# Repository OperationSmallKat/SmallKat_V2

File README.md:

# Small Kat Quadruped

The SmallKat project is a low cost, opensource, 3D printed quadrupedal platform designed and made by 2 WPI students (Keion Bisland and Xavier Little) along with framework code prepared by Kevin Harrington. The intention of the platform was to make a dynamics quadruped for the education/research and high-end toy markets. Using hobby servos and common electronics allows the overall price point to remain very low in comparison to its competitors. 

SmallKat comes in 3 sizes, micro, small and xl. Micro is the smallest and at one pound, is the same size and weight as a kitten. Small is the current product offering and is availible in 2 different electronics solutions. XL is a research grade platform and is the product of an MQP at WPI. 

The simple electronics platform is a single ESP32, 16 servos, 3 switch mode BEC's and a BNO055 IMU.  This platform is easiest to source assemble using of OTS parts plus printed pieces. This platform streams sensor data up, and servo positions down, using the WiFi built into the ESP32. This configuration is easy to develop for because the code kinematics/walking gait code runs on a nearby PC. Kinematics and walking gait/body controllers can be swapped out on-the-fly without restarting SmallKats controller making development fast. Once algorithms are finalized and published to Git, they can be loaded by the second configuration and run in a tight real-time loop with the hardware. A downside to this configuration is that it is only as stable as your WiFi signal in the room. 

The advanced configuration uses the same control coda as the Wifi version, except it loads a headless kernel and runs it  on a RasPi onboard of the robot. This configuration uses an STM32 to connect to the BNO055 and servos, and bridge them directly to the onboard RasPi over HID.  The first variant used a Teensy, but we wish for the full stack to be fully open source and so are switching to a custom STM32 board.  This solution will be more expensive, and development loops will include pusing to a git server and re-starting the robots control stack to load new code. These trade offs suggest that both electronics solutions ought to exist as options, and researchers might want both in a given lab. Toy markets would only be interested in this type of fully stand-alone electronics, since it requires no setup to start the robot running.

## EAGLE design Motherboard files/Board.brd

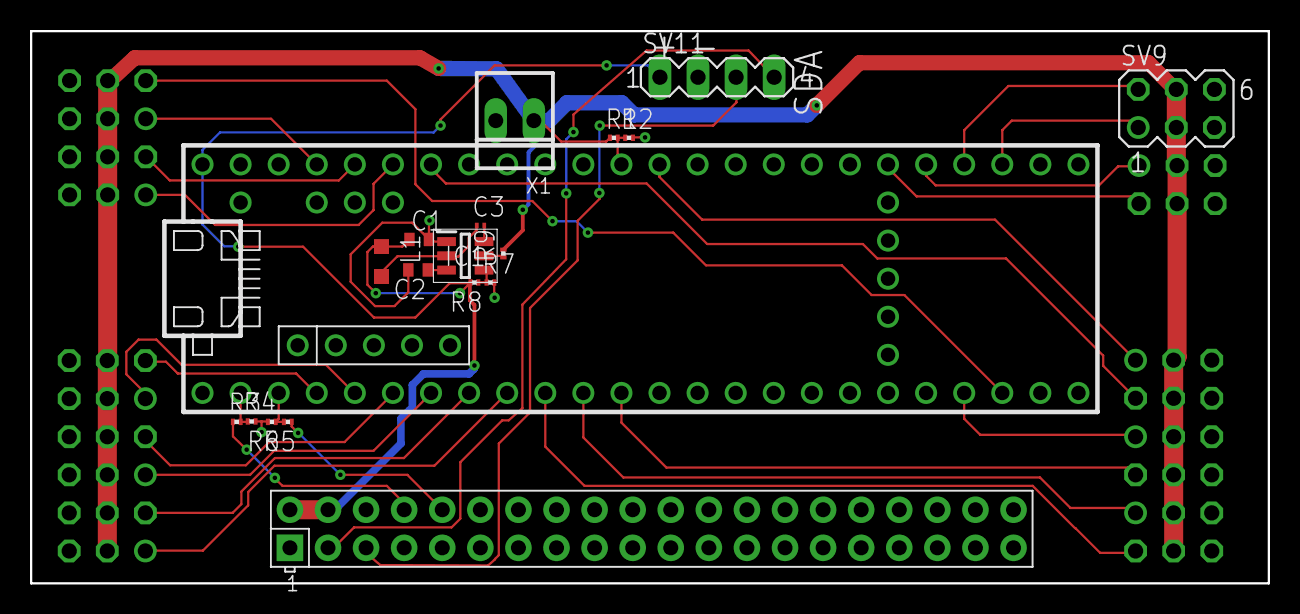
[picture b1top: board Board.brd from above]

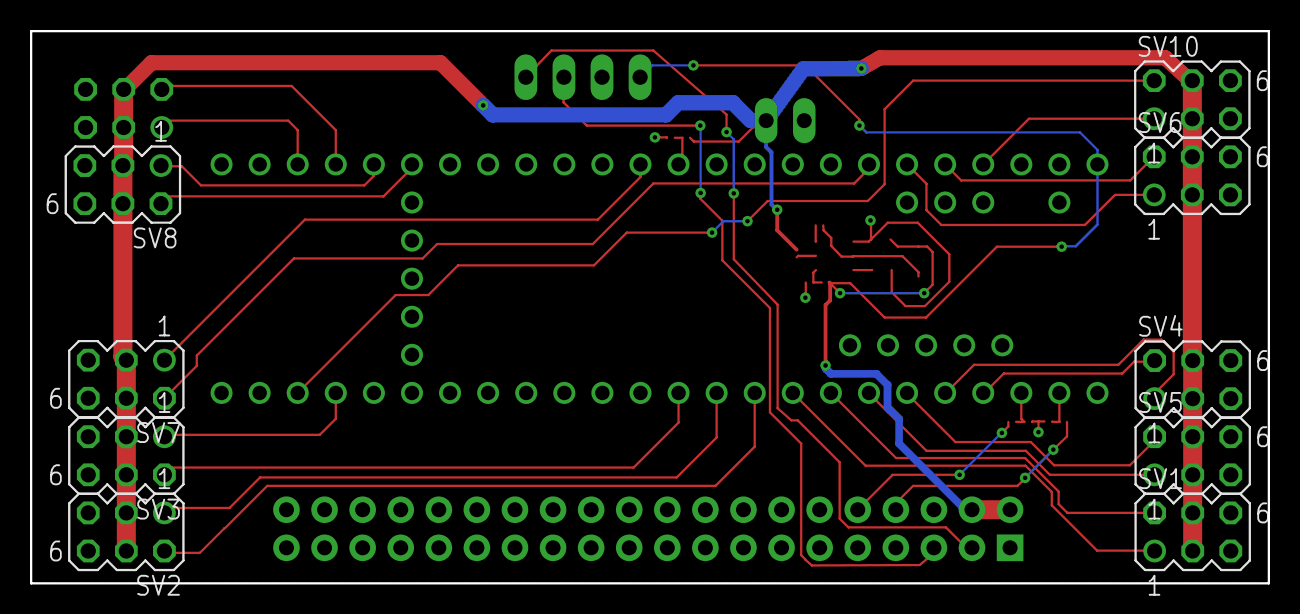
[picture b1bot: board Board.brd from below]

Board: 2 copper layers, 82.5 x 36.8 mm, 28 parts (9 on the bottom side), 35 nets.

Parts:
C1, C2: C0402
C3: C0201
IC1: TPS562209DDCR; SOT95P280X110-6N
L1: L2012C
R1, R2, R3, R4, R5, R6, R7, R8, R9: R0201
SV1, SV2, SV3, SV4, SV5, SV6, SV7, SV8, SV9, SV10: MA03-2
SV11: MA04-1
U$1: RPI-ZERO; RASPBERRYPI_BASTELSTUBE_V13_RASPI_BOARD_B+_FULL
U$2: TEENSY_3.5/3.6
X1: 22-23-2021

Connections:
+5V: C1.1, L1.1, R8.2, SV11.1, U$1.2, U$1.4, U$2.VIN
BATTCHECK: R1.2, R2.1, U$2.15/A1
GND: C1.2, C2.2, IC1.1, R2.2, R4.2, R6.2, R7.2, SV1.5, SV1.6, SV2.5, SV2.6, SV3.5, SV3.6, SV4.5, SV4.6, SV5.5, SV5.6, SV6.5, SV6.6, SV7.5, SV7.6, SV8.5, SV8.6, SV9.5, SV9.6, SV10.5, SV10.6, SV11.2, U$1.6, U$1.9, U$1.14, U$1.20, U$1.25, U$1.30, U$1.34, U$1.39, U$2.AGND, U$2.GND, U$2.GND2, X1.2
unnamed: C3.1, IC1.2, L1.2
unnamed: C2.1, IC1.3
unnamed: C3.2, IC1.6
unnamed: IC1.5, R9.1
unnamed: IC1.4, R7.1, R8.1
RPIRX: R5.1, U$1.10
RPITX: R3.1, U$1.8
RX: R3.2, R4.1, U$2.0/RX
S1: SV4.2, U$2.2
S2: SV4.1, U$2.3/CANTX
S3: SV5.2, U$2.4/CANRX
S4: SV5.1, U$2.5
S5: SV1.2, U$2.6
S6: SV1.1, U$2.7
S7: SV2.2, U$2.8
S8: SV2.1, U$2.9/CS
S9: SV3.2, U$2.10/CS
S10: SV3.1, U$2.29
S11: SV10.2, U$2.30
S12: SV10.1, U$2.23/A9
S13: SV6.2, U$2.22/A8
S14: SV6.1, U$2.21/A7
S15: SV7.2, U$2.20/A6
S16: SV7.1, U$2.14/A0
S17: SV8.2, U$2.38/A19
S18: SV8.1, U$2.37/A18
S19: SV9.2, U$2.36/A17
S20: SV9.1, U$2.35/A16
SCL: SV11.3, U$1.5
SDA: SV11.4, U$1.3
TX: R5.2, R6.1, U$2.1/TX
VCC: R1.1, R9.2, SV1.3, SV1.4, SV2.3, SV2.4, SV3.3, SV3.4, SV4.3, SV4.4, SV5.3, SV5.4, SV6.3, SV6.4, SV7.3, SV7.4, SV8.3, SV8.4, SV9.3, SV9.4, SV10.3, SV10.4, X1.1

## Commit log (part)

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2018-05-18 MediumKat STL files
2018-05-18 Added MKBody
2018-05-18 added the lowe limbs
2018-05-18 all STL files updated
2018-05-18 first limb update
2018-05-18 lims corrected
2018-05-18 first leg placement working
2018-05-18 renamed limbs
2018-05-18 working on DH parameters
2018-05-18 Fixed Legs
2018-05-18 Leg DH parameters and config
2018-05-18 Edited legs
2018-05-18 added tail and head files
2018-05-18 tried to add cat and head
2018-05-19 head and tail index update
2018-05-19 head and tail loading
2018-05-19 updating link indexes
2018-05-19 non-overlapping links
2018-05-19 orentation of neack matches links
2018-05-19 allignment of neck stl
2018-05-19 neck location
2018-05-19 head and tail root locations
2018-05-19 base of limbs and D-H for neck and tail
2018-05-19 head located
2018-05-19 all cat parts loading nicely
2018-05-19 all cat parts loading
2018-05-19 shoulder reorentation
2018-05-19 walking engine loaded
2018-05-19 working defaults
2018-05-19 right rear boundaries
2018-05-19 front left bounded
2018-05-19 dynamic walk cycle
2018-05-20 step reset working
2018-05-21 adding the simple API
2018-05-21 syntax
2018-05-21 IMU and servo device
2018-05-21 adding the import for IMU
2018-05-21 update vidpid pair
2018-05-21 better printouts
2018-05-21 updating the IMU data
2018-05-21 tighter gait
2018-05-21 updated the link angles
2018-05-21 wider hip kinematics
2018-05-21 calculating the gat section percentages based on time
2018-05-22 step step down working in slow mo
2018-05-22 rear left adjusted
2018-05-22 walking in tuning
2018-05-22 mostly working trot gait
2018-05-22 mystery step reset issue
2018-05-22 no runaway feet
2018-05-22 foot cycling for up section
2018-05-22 dynamic walking gait
2018-05-22 smaller transit to home
2018-05-22 drift fix
2018-05-22 no prints
2018-05-22 trapazoidal foot motion profile
2018-05-22 modular cycle grouping
2018-05-22 working dynamic wave gait
2018-05-22 adding IMU print to dynamics
2018-05-22 adding listeners
2018-05-22 removing IMU in loop
2018-05-22 IMU integrated into walking gait
2018-05-22 dynamic gait
2018-05-22 normal speed
2018-05-22 adjustable pan and tilt values
2018-05-22 normal shoulder gait
2018-05-22 parametric static offsets
2018-05-22 latest dynamics
2018-05-22 Walking (#4)
    * trapazoidal foot motion profile
    * modular cycle grouping
    * working dynamic wave gait
    * adding IMU print to dynamics
    * adding listeners
    * removing IMU in loop
2018-05-23 removing dead links
2018-05-23 removed stub links
2018-05-23 catch NPE
2018-05-23 ensuring push
2018-05-24 Config
2018-05-24 updated upper and lower bounds
2018-05-24 updated centers
2018-05-24 updated a theta
2018-05-24 changing dh parameters
2018-05-24 50.80
2018-05-25 adding coriolius updater
2018-05-25 swagger
2018-05-25 adding the timeouts back in
2018-05-25 smooth bobbing to shif balence
2018-05-25 at-speed walking with head and tail bob
2018-05-25 heat crests at the weaight shift point
2018-05-25 standard smoothed bobbing unless UMU updates
2018-05-25 dynamic step gait timing
2018-05-25 adding dynamic speed updates
2018-05-25 dynamic loop speed based on ground speed
2018-05-25 cleaned up the step reset cycle trajectory loop
2018-05-25 full dynamics with all legs
2018-05-25 corrected maximum step size
2018-05-25 no motion when stopped
2018-05-25 full trajectory step cycle working
2018-05-25 catch teh multi-set exception
2018-05-25 proper step loop resetting
2018-05-25 time gap the recalulation loop
2018-05-25 using the step cycle count to determ pan value
2018-05-25 timeout of commands
2018-05-25 wait for the previous command to finish
2018-05-25 bound velocity but not overall translation
2018-05-25 cached the pose, lets use this as the target later
2018-05-25 set the global transform
2018-05-25 cached positions for avoiding collisions
2018-05-25 full stack full cycle walking gait, no hiicups
2018-05-25 working cycle
2018-05-26 adding possiblity checks to sets
2018-05-26 Force homing even is pathing errors occour
2018-05-26 attempt to use the set joint values first
2018-05-26 updaed dynamisc walking
2018-05-26 adding the tripod style gait
2018-05-26 modularized the building of the leg groups
2018-05-26 comments
2018-05-26 waiting on the timeout, not the timouut vatiable to accept a new command
2018-05-26 bount gait percentage to 1
2018-05-26 bounding the step lenght appropratly
2018-05-26 stop impossible pose update from executing
2018-05-26 fail out pose updates that are not possible
2018-05-26 parameterize the minimum step over time as the minimum gait time
2018-05-26 Dynamics (#5)
    * trapazoidal foot motion profile
    * modular cycle grouping
    * working dynamic wave gait
    * adding IMU print to dynamics
    * adding listeners
    * removing IMU in loop
2018-05-26 stop the head bob when stepping home
2018-05-27 boundary orented step calculations
2018-05-27 more complete checking of the possiblibility of a new update for a leg
2018-05-27 clearly bounding the possible foot locations and checking all extrema
2018-05-27 full cycle dynamics
2018-05-27 faster compute cycle
2018-05-27 timer reset by the main thread calls, not the walking thread calls
2018-05-27 startup state for first walk cycle starting in the current state
2018-05-27 sitting after steps timeout
2018-05-27 sitting at the end of a loop
2018-05-27 approoprate walking and sitting at the end of a loop
2018-05-27 updating the head and neck in the sit down loop
2018-05-27 smoother sitting
2018-05-27 sitting and standing interpolated based on loop timeing
2018-05-27 sleep in the correct space
2018-05-27 longer sit timeout
2018-05-27 Simulate the cat with custome physics engine
2018-05-27 adding basic physics
2018-05-28 catch exceptions in new pose
2018-05-28 calibrating...
2018-05-28 if not a Kat, do not sit
2018-05-28 Creating a robot loading script
2018-05-28 updating urls
2018-05-28 load cat from script side-loader
2018-05-28 fixed the limb link startup problem
2018-05-30 limits to keep gait happy
2018-05-30 filex the links bak, der
2018-05-30 adding tighter coriolis loop
2018-05-30 updated limits for kineamtics
2018-05-30 updated limits for kinematics
2018-05-31 Configuring Cat
2018-05-31 Configured
2018-06-03 Dynamics (#6)
    * limits to keep gait happy
    * filex the links bak, der
    * adding tighter coriolis loop
    * kinematics bounding
    * updated limits for kineamtics
    * updated limits for kinematics
2018-06-03 Adding arguments to the robot loading script
2018-06-03 adding parameters to the launch script call of the robot loader
2018-06-06 removed enum
2018-06-06 changing bottom link limits
2018-06-06 front feet a bit forward
2018-06-06 all gait cycles even
2018-06-06 remove dead code
2018-06-06 tighten the hip limits
2018-06-06 good speed over range
2018-06-06 adding tilt control
2018-06-06 moving leg back
2018-06-06 corrected pose
2018-06-06 posing is working
2018-06-06 better full speed turining
2018-06-06 fixed misallignment
2018-06-07 final calibration against hardware
2018-06-08 calibrated head and tail
2018-06-08 negative scale
2018-06-08 negative scales
2018-06-08 centered tail
2018-06-08 changed calibration
2018-06-08 Recalibrated
2018-06-12 Moved Firmware
2018-06-13 updaing URLs
2018-06-13 updaing URL's
2018-06-13 Removing files moved to new repos
2018-06-13 updating URL
2018-07-10 updated teh defaults
2018-07-10 changed home v alues
2018-07-17 calibrate
2018-07-17 reversing the hips
2018-07-18 use the UDP stack to get a udp version of the controller if its availible
2018-07-25 bugfix
2018-07-25 catch
2018-09-13 better prints
2018-09-13 using new controller API
2018-11-30 Updated order
2018-11-30 Updated head pinout
2018-11-30 updated stepover
2018-11-30 head range
2018-11-30 tal calibrate
2018-11-30 tail bounds
2018-11-30 rear conf
2018-11-30 calibrate legs
2018-11-30 faster timeout
2018-12-08 tweak limits
2019-03-15 removing IMU
2019-03-15 adding imu back
2019-03-15 adding the newest simple packet coms
2019-03-15 faster loops
2019-03-15 adding timeot
2019-03-15 adding the timepouts
2019-03-15 longer steps
2019-03-15 walking gait
2019-03-15 calibrate head
2019-03-15 calibrate tail
2019-03-20 no sit
2019-03-20 step home
2019-03-20 no step reset
2019-03-20 walking working
2019-03-20 config walking
2019-03-20 sitting reenabled
2019-03-20 changed the control
2019-03-20 adding game controller loading to the single loading script
2019-03-20 adding game controller
2019-03-20 adding virtual mode print
2019-03-21 stable loading of game controller
2019-03-21 working robot loading
2019-03-21 use the common version between simple packetcoms
2019-03-21 working loading two different udp devices without crosstalk
2019-03-22 more stepover
2019-03-22 head angle back to normal
2019-03-22 laod robot
2019-03-22 walking cycle
2019-03-22 higher stepover
2019-03-22 walking working well
2019-03-26 front legs forward
2019-03-29 alking gait update
2019-04-05 catch missing controller
2019-04-05 maor bobbing
2019-04-05 waking stabalized
2019-04-12 calibrations
2019-04-12 WALKING OFFSETS
2019-04-12 calibration
2019-04-12 walking update
2019-04-12 tail swing
2019-04-12 cat walking
2019-04-15 removing dynamics
2019-04-15 switching to angular position for IMU update
2019-04-15 adding in link limits to link setting
2019-04-16 head pan opisite
2019-04-16 more extreame gain
2019-04-16 faster coriolis
2019-04-16 stop after walking
2019-04-16 orking
2019-04-17 tilt while walking
2019-04-17 Adding a dynamic tilting to the walking cycle
2019-04-17 cleaner
2019-04-17 corrected tilt
2019-04-17 walking tilt helping
2019-04-17 added a sin component
2019-04-18 changing the tilt
2019-04-25 adding a second thread for the servo packets
2019-04-25 adding the second servo command system
2019-04-27 updating the downstream buffer
2019-04-27 longer timeout
2019-04-27 adding upstream reads
2019-04-27 updating to coriolis as priority if tipping
2019-04-28 walking gait is working well
2019-05-01 use side load script for game controller loading
2019-05-01 lower timeouts
2019-05-02 better compositing of swing and coriolis
2019-05-02 better sit behavior
2019-05-02 dynamic side step easier than i thought!
2019-05-02 better posing
2019-05-05 latteral move helping kick legs out
2019-05-05 removed spurrious feducial set
2019-05-05 sitting pose
2019-05-06 slower loop
2019-05-07 z move added back to loop
2019-05-07 less agressive walking
2019-05-07 tilt angle
2019-05-07 setpoint as current
2019-05-07 better up data
2019-05-07 alngle update
2019-05-07 walking shuts down ok
2019-05-28 changing the sit angle
2019-06-05 removing the pose update
2019-06-06 adding walking loop moveing pose
2019-07-08 new launcher
2019-07-08 adding the deps
2019-07-10 no re-pose
2019-07-11 check angle before setting
2019-07-18 updating the mechanism for searching for device names
2019-07-18 tested new name system
2019-07-26 fixing tail spin error
2019-07-27 working dynamics
2019-07-28 pushing code
2019-08-06 eliminate sit angle
2019-08-16 calibrated
2019-11-04 adding imports to make the loading in eclipse clean
2019-12-03 updateing simple packet coms
2019-12-09 Fixed Body
2019-12-18 adding configs
2019-12-18 moving the imu
2019-12-18 fixing the imu center
2019-12-18 fixing the xml
2019-12-18 updating the cat
2019-12-19 fixing the exception
2019-12-19 exceptio
2019-12-19 removing junk print
2019-12-29 updating the walking
2019-12-29 setting the device name
2019-12-29 adding the name set path
2020-01-31 moving the device loader into the link loader script
2020-01-31 removing the hid dep
2020-01-31 putting it back
2020-03-11 fixed the npe
2021-02-05 Bowler/DynamicWalkingV2.groovy
2021-02-05 adding code
2021-02-05 Ignore the project files
2021-02-05 new body controller with fixed real-time loop
2021-02-05 fixing the loop steps calculation
2021-02-05 returning engine
2021-02-06 fixwd the game control version
2021-02-09 remove junk cat call
2021-02-09 remove more cat calls
2021-02-09 updated walking
2021-02-10 flip if upside down
2021-02-10 no junk intermediate points
2021-02-10 moved dyn
2021-02-16 start and stop the gait
2021-02-18 better walking
2021-02-20 more tail
2021-02-21 use the internal home provider
2021-02-22 formatting
2021-02-26 keep the tail up
2021-02-26 updated variables
2021-03-01 moving signs
2022-03-29 update imports
2022-03-29 no imports
